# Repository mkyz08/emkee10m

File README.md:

# emkee10m

## 説明

自作キーボードの勉強用に作成したキーボード。
3x3列 + 1キーで、右下の1キーはレイヤーキー。

## Parts

- PCB：1個
- ボトムプレート：1個
- トッププレート：1個
- キースイッチ（MX or Choc）：10個
- キーキャップ 1U：10個
- Pro Micro：1個
- ダイオード　1N4148：10個
- タクトスイッチ　MJ-4PP-9：1個
- Underglow LED　WS2812（オプション）：1つ
- マイクロUSBケーブル：1本
- M2ネジ(8mm)：12個
- M2スペーサ(4mm)：9個
- ゴム足：4個

## ファームウェア

```
make emkee10m:default:avrdude
```

## デフォルトキー配列

## ビルドログ

- ダイオードの実装
- タクトスイッチの実装
- Pro Microヘッダーピンの実装
- トッププレートにスイッチに嵌めて半田付け
- ボトムプレートを取付
- Pro Microのカバープレートを取付
- キーキャップを嵌める
- Pro Micro にファームウェアを書き込む

## ライセンス

MITライセンス

footprintは以下を利用しています。

- https://github.com/foostan/kbd

Copyright (c) 2018 foostan

MITライセンス

## リリースノート

- v1.0
   - 初版リリース。
- v1.1（修正中）
  - スイッチの取付位置を裏から表に変更
  - Pro MicroのUSB取り付けに余裕がなかったため、外側へ移動（数mm）程度
  - PCBのM2ねじ用のMHを大きく変更

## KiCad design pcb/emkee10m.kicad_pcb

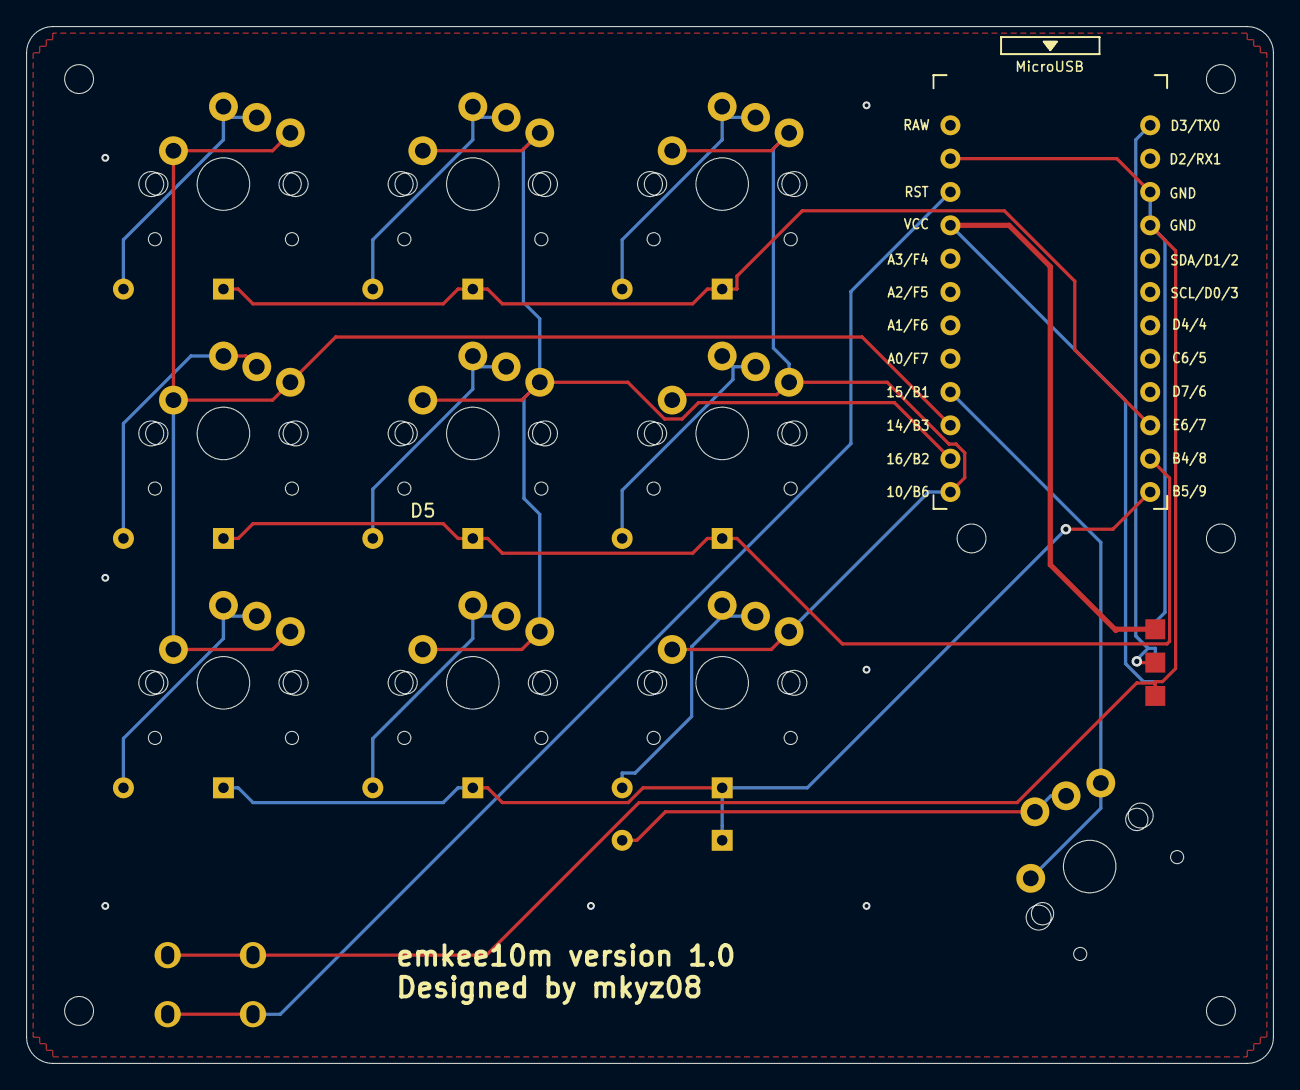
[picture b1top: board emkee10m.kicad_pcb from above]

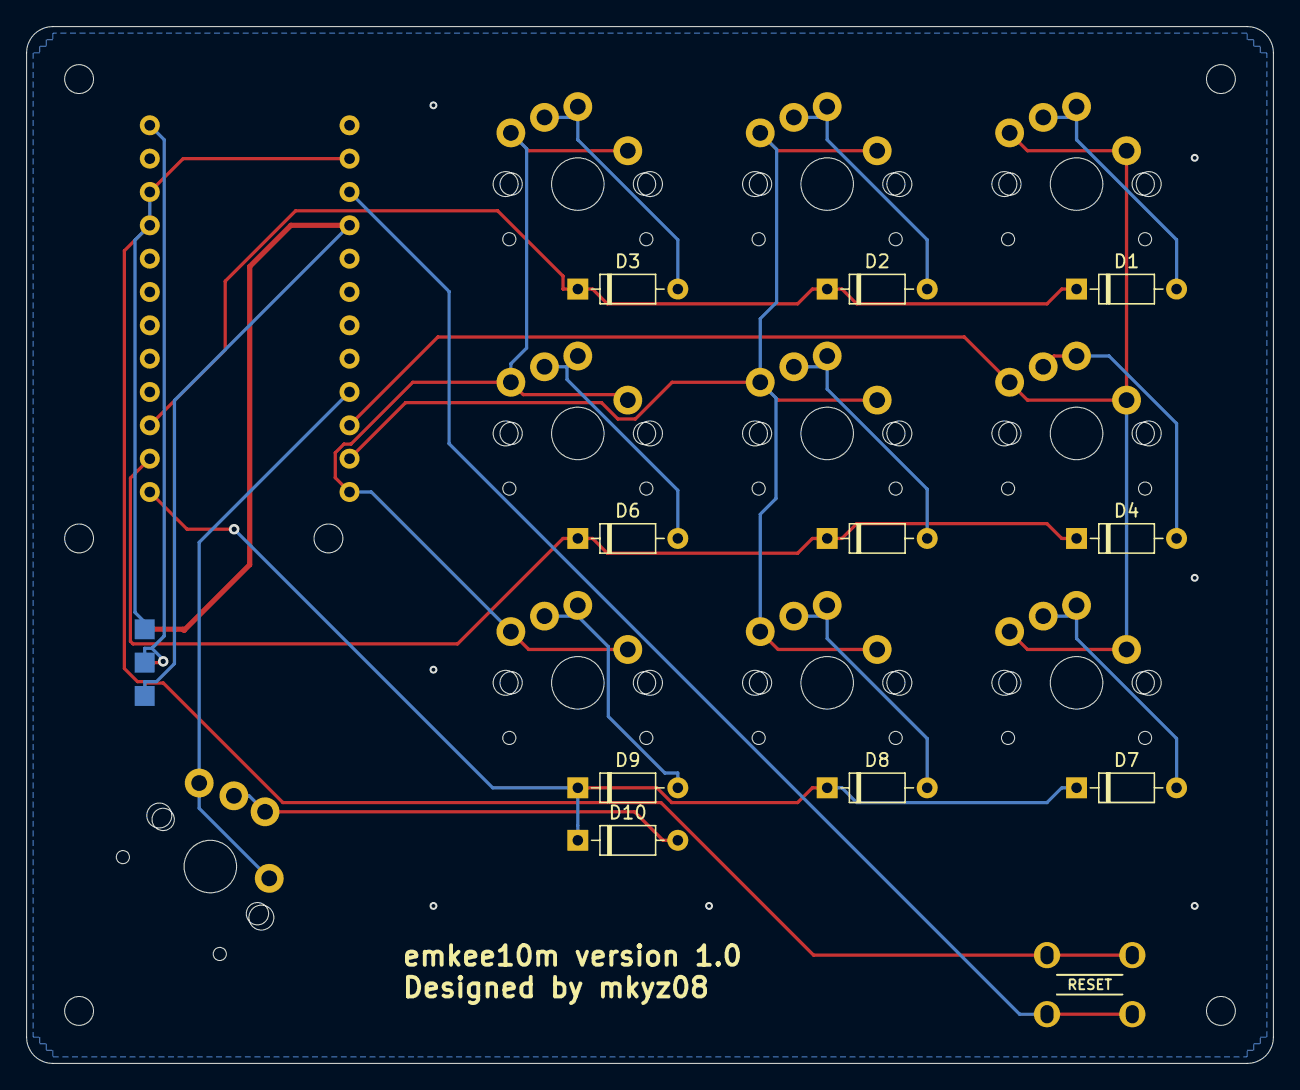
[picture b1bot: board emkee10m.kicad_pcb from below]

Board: 2 copper layers, 95.0 x 79.0 mm, 29 parts (12 on the bottom side), 21 nets.

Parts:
D1, D2, D3, D4, D5, D6, D7, D8, D9, D10: 1N4148; D_DO-35_SOD27_P7.62mm_Horizontal
J1: LED; StripLED_rev
MH1, MH1#2, MH3, MH4, MH5, MH6: MountingHole_2.2mm_M2
SW1, SW2, SW3, SW4, SW5, SW6, SW7, SW8, SW9, SW10: SW_PUSH; CherryMX_Choc_1u_a
SW_REST1: SW_PUSH; ResetSW_4
U1: ProMicro; ProMicro_v3.5

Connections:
COL0: SW3.1, SW6.1, SW9.1, U1.13
COL1: SW2.1, SW5.1, SW8.1, U1.14
COL2: SW1.1, SW4.1, SW7.1, U1.15
COL3: SW10.1, U1.16
GND: J1.3, SW_REST1.1, U1.3, U1.4, U1.23
LED: J1.2, U1.1
unnamed: D1.2, SW1.2
unnamed: D2.2, SW2.2
unnamed: D3.2, SW3.2
unnamed: D4.2, SW4.2
unnamed: D5.2, SW5.2
unnamed: D6.2, SW6.2
unnamed: D7.2, SW7.2
unnamed: D8.2, SW8.2
unnamed: D9.2, SW9.2
unnamed: D10.2, SW10.2
unnamed: SW_REST1.2, U1.22
ROW0: D7.1, D8.1, D9.1, D10.1, U1.12
ROW1: D4.1, D5.1, D6.1, U1.11
ROW2: D1.1, D2.1, D3.1, U1.10
VCC: J1.1, U1.21

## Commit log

2020-02-29 [Add] v1.0
2020-02-29 [Update] README修正
2020-02-29 [Update] ライセンスについて追記
